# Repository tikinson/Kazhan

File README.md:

# 🦇Kazhan🦇

28 Keys. MX and Choc compatible keyboard with CH552T controller. This is the next logical step after my experimental keyboard [ToadsTempest](https://github.com/tikinson/ToadsTempest).

## Idea

Kazhan (Кажан) is derived from the Ukrainian word meaning "bat".
As a fan of ZilpZalp/Hummingbird projects i decided make something with same layout but more personalized. Same but different.

## What this project is and what it is not

### Goals:
- A pet project of a keyboard as an act of absolute self-expression.
- Flexibility and experiments over (and maybe in some case against) minimalistic design approach.
- Testing interesting "non - conventional" switches as extra keys.
- Testing things that i don't saw (yet?) in another keyboard PCB designs.

### Non-goals:
- Creation of another variant of the Corne (I like Corne btw, that was my first love in this hobby).
- Design with a definite assembly variant.
- Go through the steps in the keyboard design that I have already tried.

## Features

- Mirrored design of PCB to provide split and unibody functionality in one design.
- Alpsalpine limit switches (SW1, SW2 on schematics) as additional switches. I accidentaly understood, that MX keycap kinda fits on them (with 45 dergee rotation), so i would give them a try.
- Wired USB-C (USB 2.0) connection.
- Designed for usage with [really affordable chip](https://www.lcsc.com/product-detail/USB-ICs_WCH-Jiangsu-Qin-Heng-CH552T_C111367.html) and [F.A.K.](https://github.com/semickolon/fak?tab=readme-ov-file) firmware.
- Japanese (duplex) matrix of keys and diodes for them: first of all, it's way more easy to solder one dual diode instead of two regular, because you will never put this part with wrond polarity. And also because of type of key matrix, there is two types of dual diodes: with common anode and common cathode.

## Layout

## BOM

Opening local copy of [ibom.html](./bom/ibom.html) could save some times while soldering.

| Reference       | Value                | Footprint                                                   | Qty | LCSC      |
|-----------------|----------------------|------------------------------------------------------------|-----|-----------|
| C1, C2          | 100nF               | Capacitor_SMD:C_0402_1005Metric_Pad0.74x0.62mm_HandSolder  | 2   | C1525     |
| D1, D4, D5, D8, D9, D11, D13, D15 | BAS70-06-CAnode   | Package_TO_SOT_SMD:SOT-23                                 | 8   | C8651     |
| D2, D3, D6, D7, D10, D12, D14, D16 | BAS70-05-CCatode  | Package_TO_SOT_SMD:SOT-23                                 | 8   | C34489    |
| D17             | PMEG2010EA          | Diode_SMD:D_0402_1005Metric_Pad0.77x0.64mm_HandSolder      | 1   | C2837790  |
| D18, D19        | PWR LED             | LED_SMD:LED_0402_1005Metric                                | 2   | C130724   |
| F1              | 500mA               | Fuse:Fuse_0402_1005Metric_Pad0.77x0.64mm_HandSolder        | 1   | C210357   |
| J3              | USB_C_Receptacle_USB2.0 | Connector_USB:USB_C_Receptacle_HRO_TYPE-C-31-M-12         | 1   | C2765186  |
| R1, R6          | 10k                 | Resistor_SMD:R_0402_1005Metric_Pad0.72x0.64mm_HandSolder   | 2   | C25744    |
| R2, R3          | 5.1k                | Resistor_SMD:R_0402_1005Metric_Pad0.72x0.64mm_HandSolder   | 2   | C25905    |
| R4, R5          | 1k                  | Resistor_SMD:R_0402_1005Metric                             | 2   | C11702    |
| SW1, SW2        | ~                   | MyFootprintsCollection:SW-TH_SSCF110100                   | 2   | C470322   |
| SW4, SW6        | RESET               | KEY-SMD_4P-L4.8-W4.8-P3.70-LS6.4-TL                        | 2   | C2888968  |
| S1–S28          | Keyswitch           | SW_Hotswap_Kailh_Choc_MX_1.00u_One_Sided                   | 28  |           |
| U1, U4          | USBLC6-2SC6         | Package_TO_SOT_SMD:SOT-23-6                                | 2   | C2687116  |
| U2, U3, U5      | CH552T              | -- mixed footprints --                                     | 3   | C111367   |

#### Note: S1-S28 - is footprints for switches. You can choose between MX or Kailh Choc switches (or both if you like experiments) and solder hotswaps accordingly.

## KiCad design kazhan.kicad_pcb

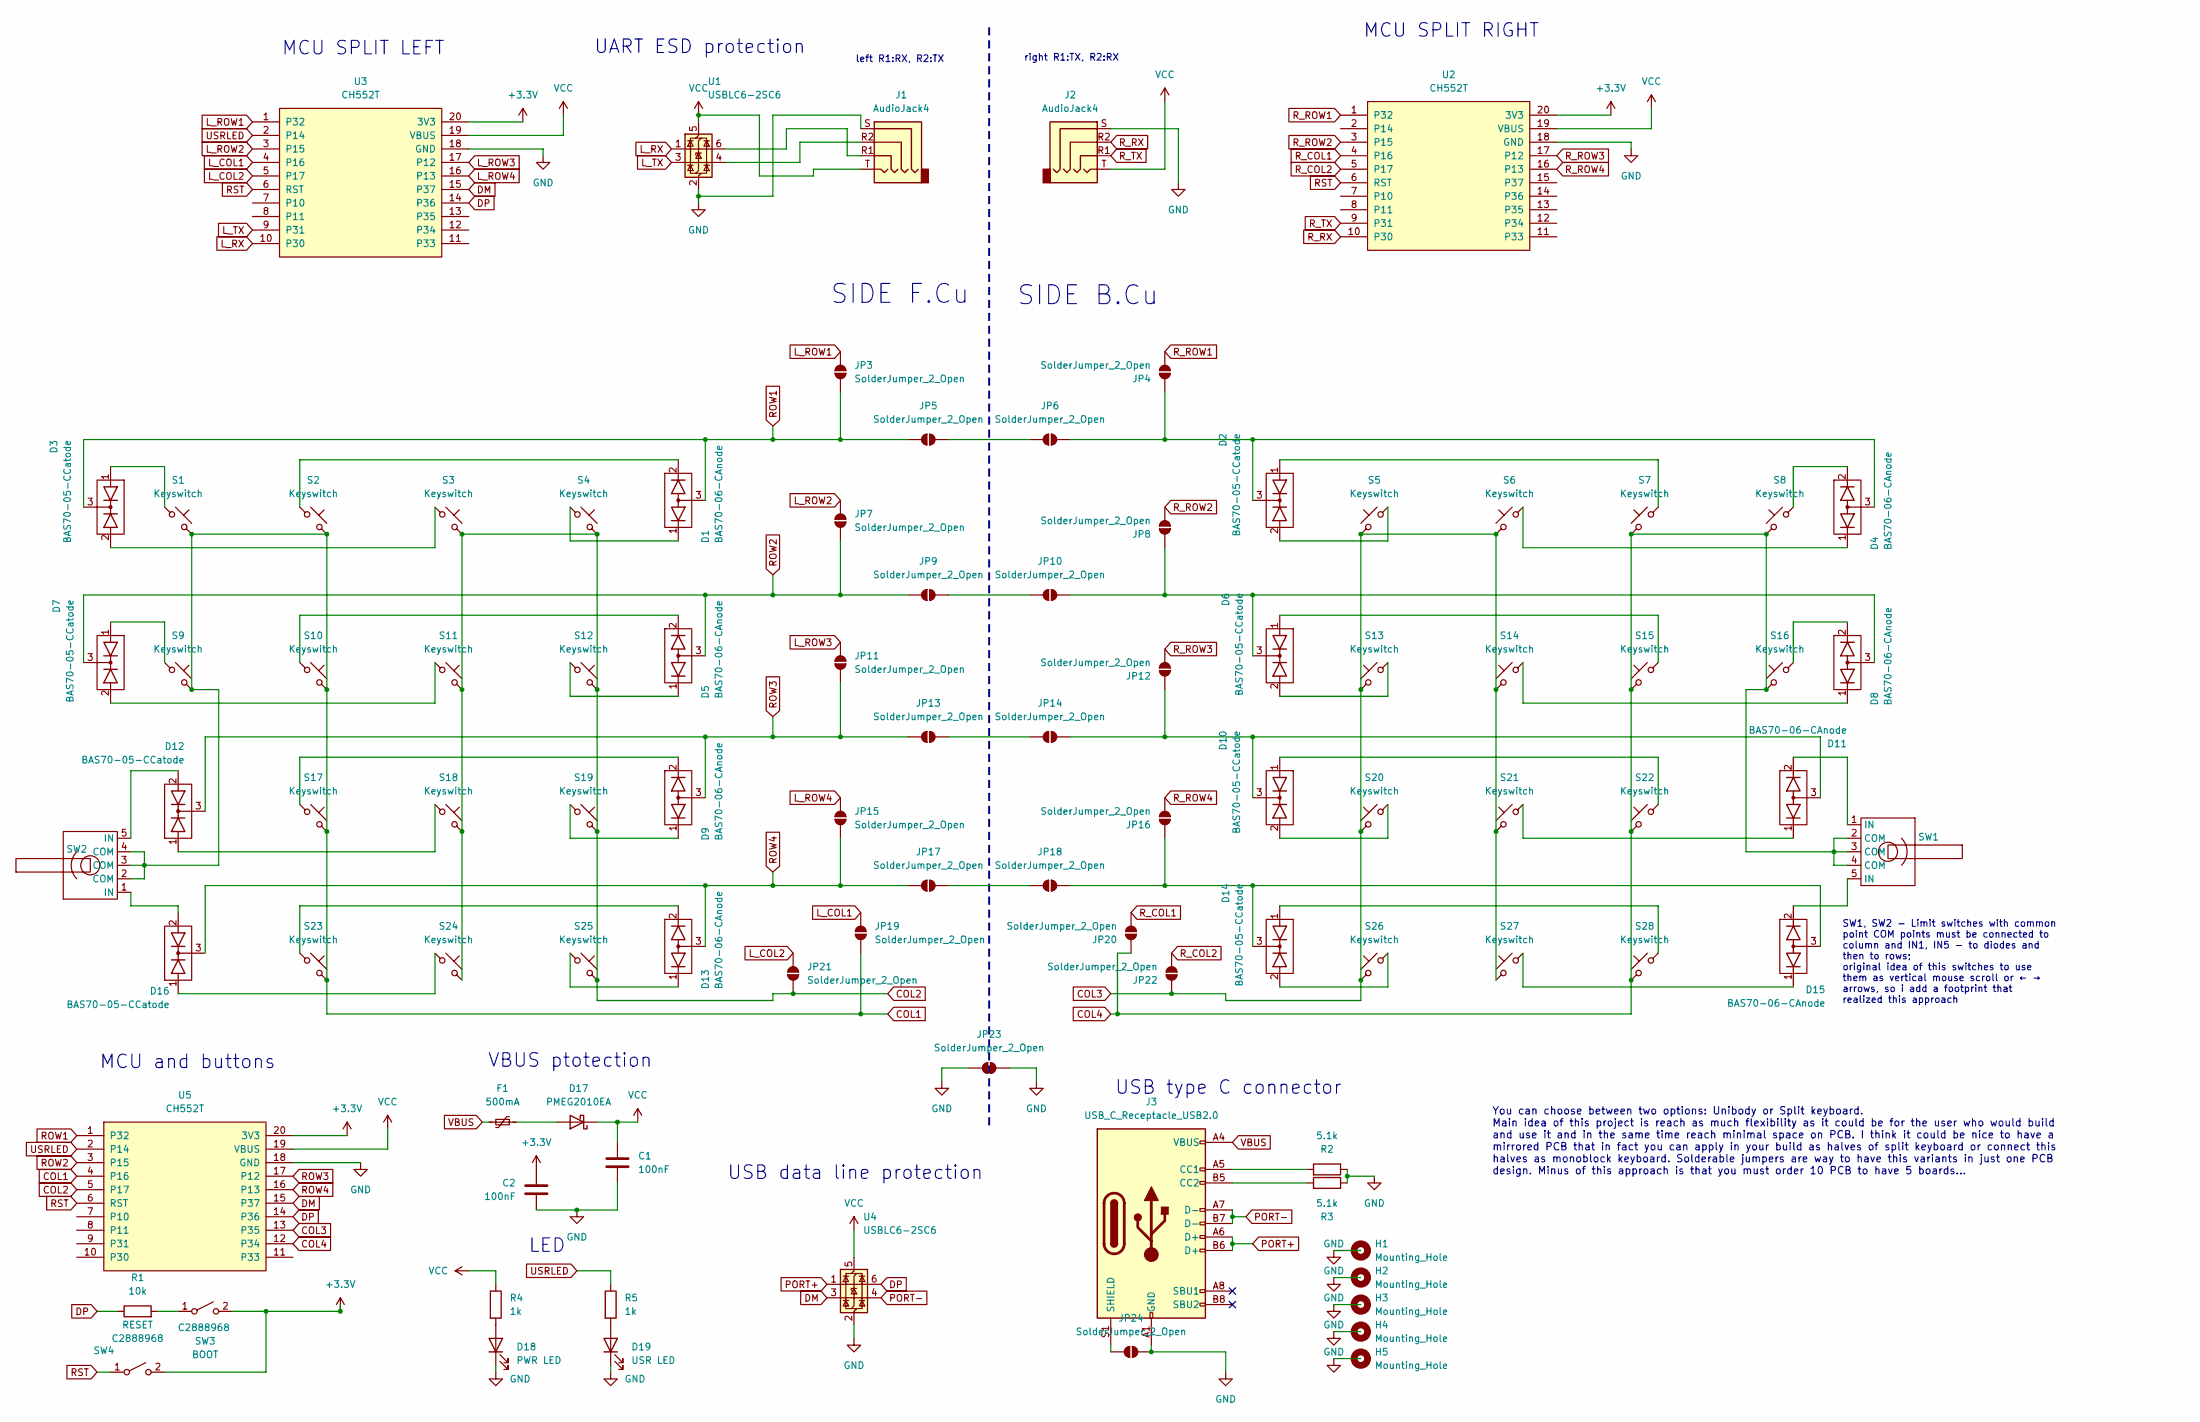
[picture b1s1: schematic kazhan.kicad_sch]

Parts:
C1, C2: 100nF; C_0402_1005Metric_Pad0.74x0.62mm_HandSolder; LCSC C1525
D1, D4, D5, D8, D9, D11, D13, D15: BAS70-06-CAnode; SOT-23
D2, D3, D6, D7, D10, D12, D14, D16: BAS70-05-CCatode; SOT-23
D17: PMEG2010EA; D_0402_1005Metric_Pad0.77x0.64mm_HandSolder; LCSC C2837790
D18: PWR LED; LED_0402_1005Metric; LCSC C130724
D19: USR LED; LED_0402_1005Metric; LCSC C130724
F1: 500mA; Fuse_0402_1005Metric_Pad0.77x0.64mm_HandSolder; LCSC C210357
H1, H2, H3, H4, H5: Mounting_Hole; MountingHole_3.5mmX4.5mm_Pad
J1: AudioJack4; PJ-320A-REVERSIBLE-F.Cu-placing
J2: AudioJack4; PJ-320A-REVERSIBLE-B.Cu-placing
J3: USB_C_Receptacle_USB2.0; USB_C_Receptacle_HRO_TYPE-C-31-M-12; JLCPCB_CORRECTION 0; -1.35; 0
JP3, JP4, JP7, JP8, JP11, JP12, JP15, JP16, JP19, JP20, JP21, JP22, JP24: SolderJumper_2_Open; SolderJumper-2_P1.3mm_Open_RoundedPad1.0x1.5mm
JP5, JP9, JP13, JP17: SolderJumper_2_Open; SolderJumper-EdgeCut-F.Cu-Placing
JP6, JP10, JP14, JP18: SolderJumper_2_Open; SolderJumper-EdgeCut-B.Cu-Placing
JP23: SolderJumper_2_Open; SolderJumper-F.Cu-B.Cu
R1: 10k; R_0402_1005Metric_Pad0.72x0.64mm_HandSolder; LCSC C25744
R2, R3: 5.1k; R_0402_1005Metric_Pad0.72x0.64mm_HandSolder; LCSC C25905
R4, R5: 1k; R_0402_1005Metric; LCSC C11702
S1, S2, S3, S4, S5, S6, S7, S8, S9, S10, S11, S12, S13, S14, S15, S16, S17, S18, S19, S20, S21, S22, S23, S24, S25, S26, S27, S28: Keyswitch; SW_Hotswap_Kailh_Choc_MX_1.00u_One_Sided
SW1, SW2: SW-TH_SSCF110100
SW3: BOOT; KEY-SMD_4P-L4.8-W4.8-P3.70-LS6.4-TL; LCSC C115357
SW4: RESET; KEY-SMD_4P-L4.8-W4.8-P3.70-LS6.4-TL; LCSC C115357
U1, U4: USBLC6-2SC6; SOT-23-6; JLCPCB_CORRECTION 0; 0; 270
U2, U3: CH552T; TSSOP-20_4.4x6.5mm_P0.65mm; LCSC C111367
U5: CH552T; TSSOP-20_4.4x6.5mm_P0.65mm-REVERSIBLE; LCSC C111367

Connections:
+3.3V: C2.1, SW3.2 (B), SW4.2 (B), U2.20 (3V3), U3.20 (3V3), U5.20 (3V3)
COL1: JP19.1 (A), S1.2, S2.2, S9.2, S10.2, S17.2, S23.2, SW2.2 (COM), SW2.3 (COM), SW2.4 (COM), U5.4 (P16)
COL2: JP21.1 (A), S3.2, S4.2, S11.2, S12.2, S18.2, S19.2, S24.2, S25.2, U5.5 (P17)
COL3: JP22.2 (B), S5.2, S6.2, S13.2, S14.2, S20.2, S21.2, S26.2, S27.2, U5.13 (P35)
COL4: JP20.2 (B), S7.2, S8.2, S15.2, S16.2, S22.2, S28.2, SW1.2 (COM), SW1.3 (COM), SW1.4 (COM), U5.12 (P34)
DM: U3.15 (P37), U4.3 (I/O2), U5.15 (P37)
DP: R1.1, U3.14 (P36), U4.6 (I/O1), U5.14 (P36)
GND: C1.2, C2.2, D18.1 (K), D19.1 (K), J1.S, J2.S, J3.A1 (GND), J3.A12 (GND), J3.B1 (GND), J3.B12 (GND), JP23.1 (A), JP23.2 (B), JP24.2 (B), R2.1, R3.1, U1.2 (GND), U2.18 (GND), U3.18 (GND), U4.2 (GND), U5.18 (GND); also elsewhere on the board
L_COL1: JP19.2 (B), U3.4 (P16)
L_COL2: JP21.2 (B), U3.5 (P17)
L_ROW1: JP3.2 (B), U3.1 (P32)
L_ROW2: JP7.1 (A), U3.3 (P15)
L_ROW3: JP11.1 (A), U3.17 (P12)
L_ROW4: JP15.1 (A), U3.16 (P13)
L_RX: U1.1 (I/O1), U3.10 (P30)
L_TX: U1.3 (I/O2), U3.9 (P31)
unnamed: D1.1 (A), S4.1
unnamed: D1.2 (A), S2.1
unnamed: D2.1 (A), S7.1
unnamed: D2.2 (A), S5.1
unnamed: D2.3 (K), D4.3 (K), JP4.1 (A), JP6.2 (B)
unnamed: D3.1 (A), S1.1
unnamed: D3.2 (A), S3.1
unnamed: D4.1 (A), S6.1
unnamed: D4.2 (A), S8.1
unnamed: D5.1 (A), S12.1
unnamed: D5.2 (A), S10.1
unnamed: D6.1 (A), S15.1
unnamed: D6.2 (A), S13.1
unnamed: D6.3 (K), D8.3 (K), JP8.1 (A), JP10.2 (B)
unnamed: D7.1 (A), S9.1
unnamed: D7.2 (A), S11.1
unnamed: D8.1 (A), S14.1
unnamed: D8.2 (A), S16.1
unnamed: D9.1 (A), S19.1
unnamed: D9.2 (A), S17.1
unnamed: D10.1 (A), S22.1
unnamed: D10.2 (A), S20.1
unnamed: D10.3 (K), D11.3 (K), JP12.1 (A), JP14.2 (B)
unnamed: D11.1 (A), S21.1
unnamed: D11.2 (A), SW1.1 (IN)
unnamed: D12.1 (A), S18.1
unnamed: D12.2 (A), SW2.5 (IN)
unnamed: D13.1 (A), S25.1
unnamed: D13.2 (A), S23.1
unnamed: D14.1 (A), S28.1
unnamed: D14.2 (A), S26.1
unnamed: D14.3 (K), D15.3 (K), JP16.2 (B), JP18.2 (B)
unnamed: D15.1 (A), S27.1
unnamed: D15.2 (A), SW1.5 (IN)
unnamed: D16.1 (A), S24.1
unnamed: D16.2 (A), SW2.1 (IN)
unnamed: D17.2 (A), F1.1
unnamed: D18.2 (A), R4.2
unnamed: D19.2 (A), R5.2
unnamed: J1.R1, U1.6 (I/O1)
unnamed: J1.R2, U1.4 (I/O2)
unnamed: J3.A5 (CC1), R2.2
unnamed: J3.B5 (CC2), R3.2
unnamed: J3.S1 (SHIELD), JP24.1 (A)
unnamed: JP5.2 (B), JP6.1 (A)
unnamed: JP9.2 (B), JP10.1 (A)
unnamed: JP13.2 (B), JP14.1 (A)
unnamed: JP17.2 (B), JP18.1 (A)
unnamed: R1.2, SW3.1 (A)
PORT+: J3.A6 (D+), J3.B6 (D+), U4.1 (I/O1)
PORT-: J3.A7 (D-), J3.B7 (D-), U4.4 (I/O2)
ROW1: D1.3 (K), D3.3 (K), JP3.1 (A), JP5.1 (A), U5.1 (P32)
ROW2: D5.3 (K), D7.3 (K), JP7.2 (B), JP9.1 (A), U5.3 (P15)
ROW3: D9.3 (K), D12.3 (K), JP11.2 (B), JP13.1 (A), U5.17 (P12)
ROW4: D13.3 (K), D16.3 (K), JP15.2 (B), JP17.1 (A), U5.16 (P13)
RST: SW4.1 (A), U2.6 (RST), U3.6 (RST), U5.6 (RST)
R_COL1: JP20.1 (A), U2.4 (P16)
R_COL2: JP22.1 (A), U2.5 (P17)
R_ROW1: JP4.2 (B), U2.1 (P32)
R_ROW2: JP8.2 (B), U2.3 (P15)
R_ROW3: JP12.2 (B), U2.17 (P12)
R_ROW4: JP16.1 (A), U2.16 (P13)
R_RX: J2.R2, U2.10 (P30)
R_TX: J2.R1, U2.9 (P31)
USRLED: R5.1, U3.2 (P14), U5.2 (P14)
VBUS: F1.2, J3.A4 (VBUS), J3.A9 (VBUS), J3.B4 (VBUS), J3.B9 (VBUS)
VCC: C1.1, D17.1 (K), J1.T, J2.T, R4.1, U1.5 (VBUS), U2.19 (VBUS), U3.19 (VBUS), U4.5 (VBUS), U5.19 (VBUS)

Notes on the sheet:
SW1, SW2 - Limit switches with common point COM points must be connected to column and IN1, IN5 - to diodes and then to rows; original idea of this switches to use them as vertical mouse scroll or ← → arrows, so i add a footprint that realized this approach
You can choose between two options: Unibody or Split keyboard. Main idea of this project is reach as much flexibility as it could be for the user who would build and use it and in the same time reach minimal space on PCB. I think it could be nice to have a mirrored PCB that in fact you can apply in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
MCU and buttons
right R1:TX, R2:RX
USB type C connector
MCU SPLIT LEFT
SIDE B.Cu
USB data line protection
left R1:RX, R2:TX
MCU SPLIT RIGHT
LED
UART ESD protection
VBUS ptotection
SIDE F.Cu

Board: 2 copper layers, 96 parts (24 on the bottom side), 83 nets, no tracks yet.

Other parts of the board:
JP1, JP2: SolderJumper_2_Open; SolderJumper-2_P1.3mm_Open_RoundedPad1.0x1.5mm

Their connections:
GND: JP1.2 (B), JP2.2 (B); also elsewhere on the board

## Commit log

2024-11-23 init
2024-11-23 clean
2024-11-23 license
2024-11-23 work with readme
2024-11-23 some images
2024-11-27 outline and placing started
2024-12-01 all except matrix is routed
2024-12-11 some improvements and final design of v0
2024-12-19 upd readme
